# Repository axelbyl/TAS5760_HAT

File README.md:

# TAS5760 based Amplifier HAT for Raspberry Pi

This repository contains the KiCad files for an audio amplifier based on the class D TI TAS5760 amplifier module.

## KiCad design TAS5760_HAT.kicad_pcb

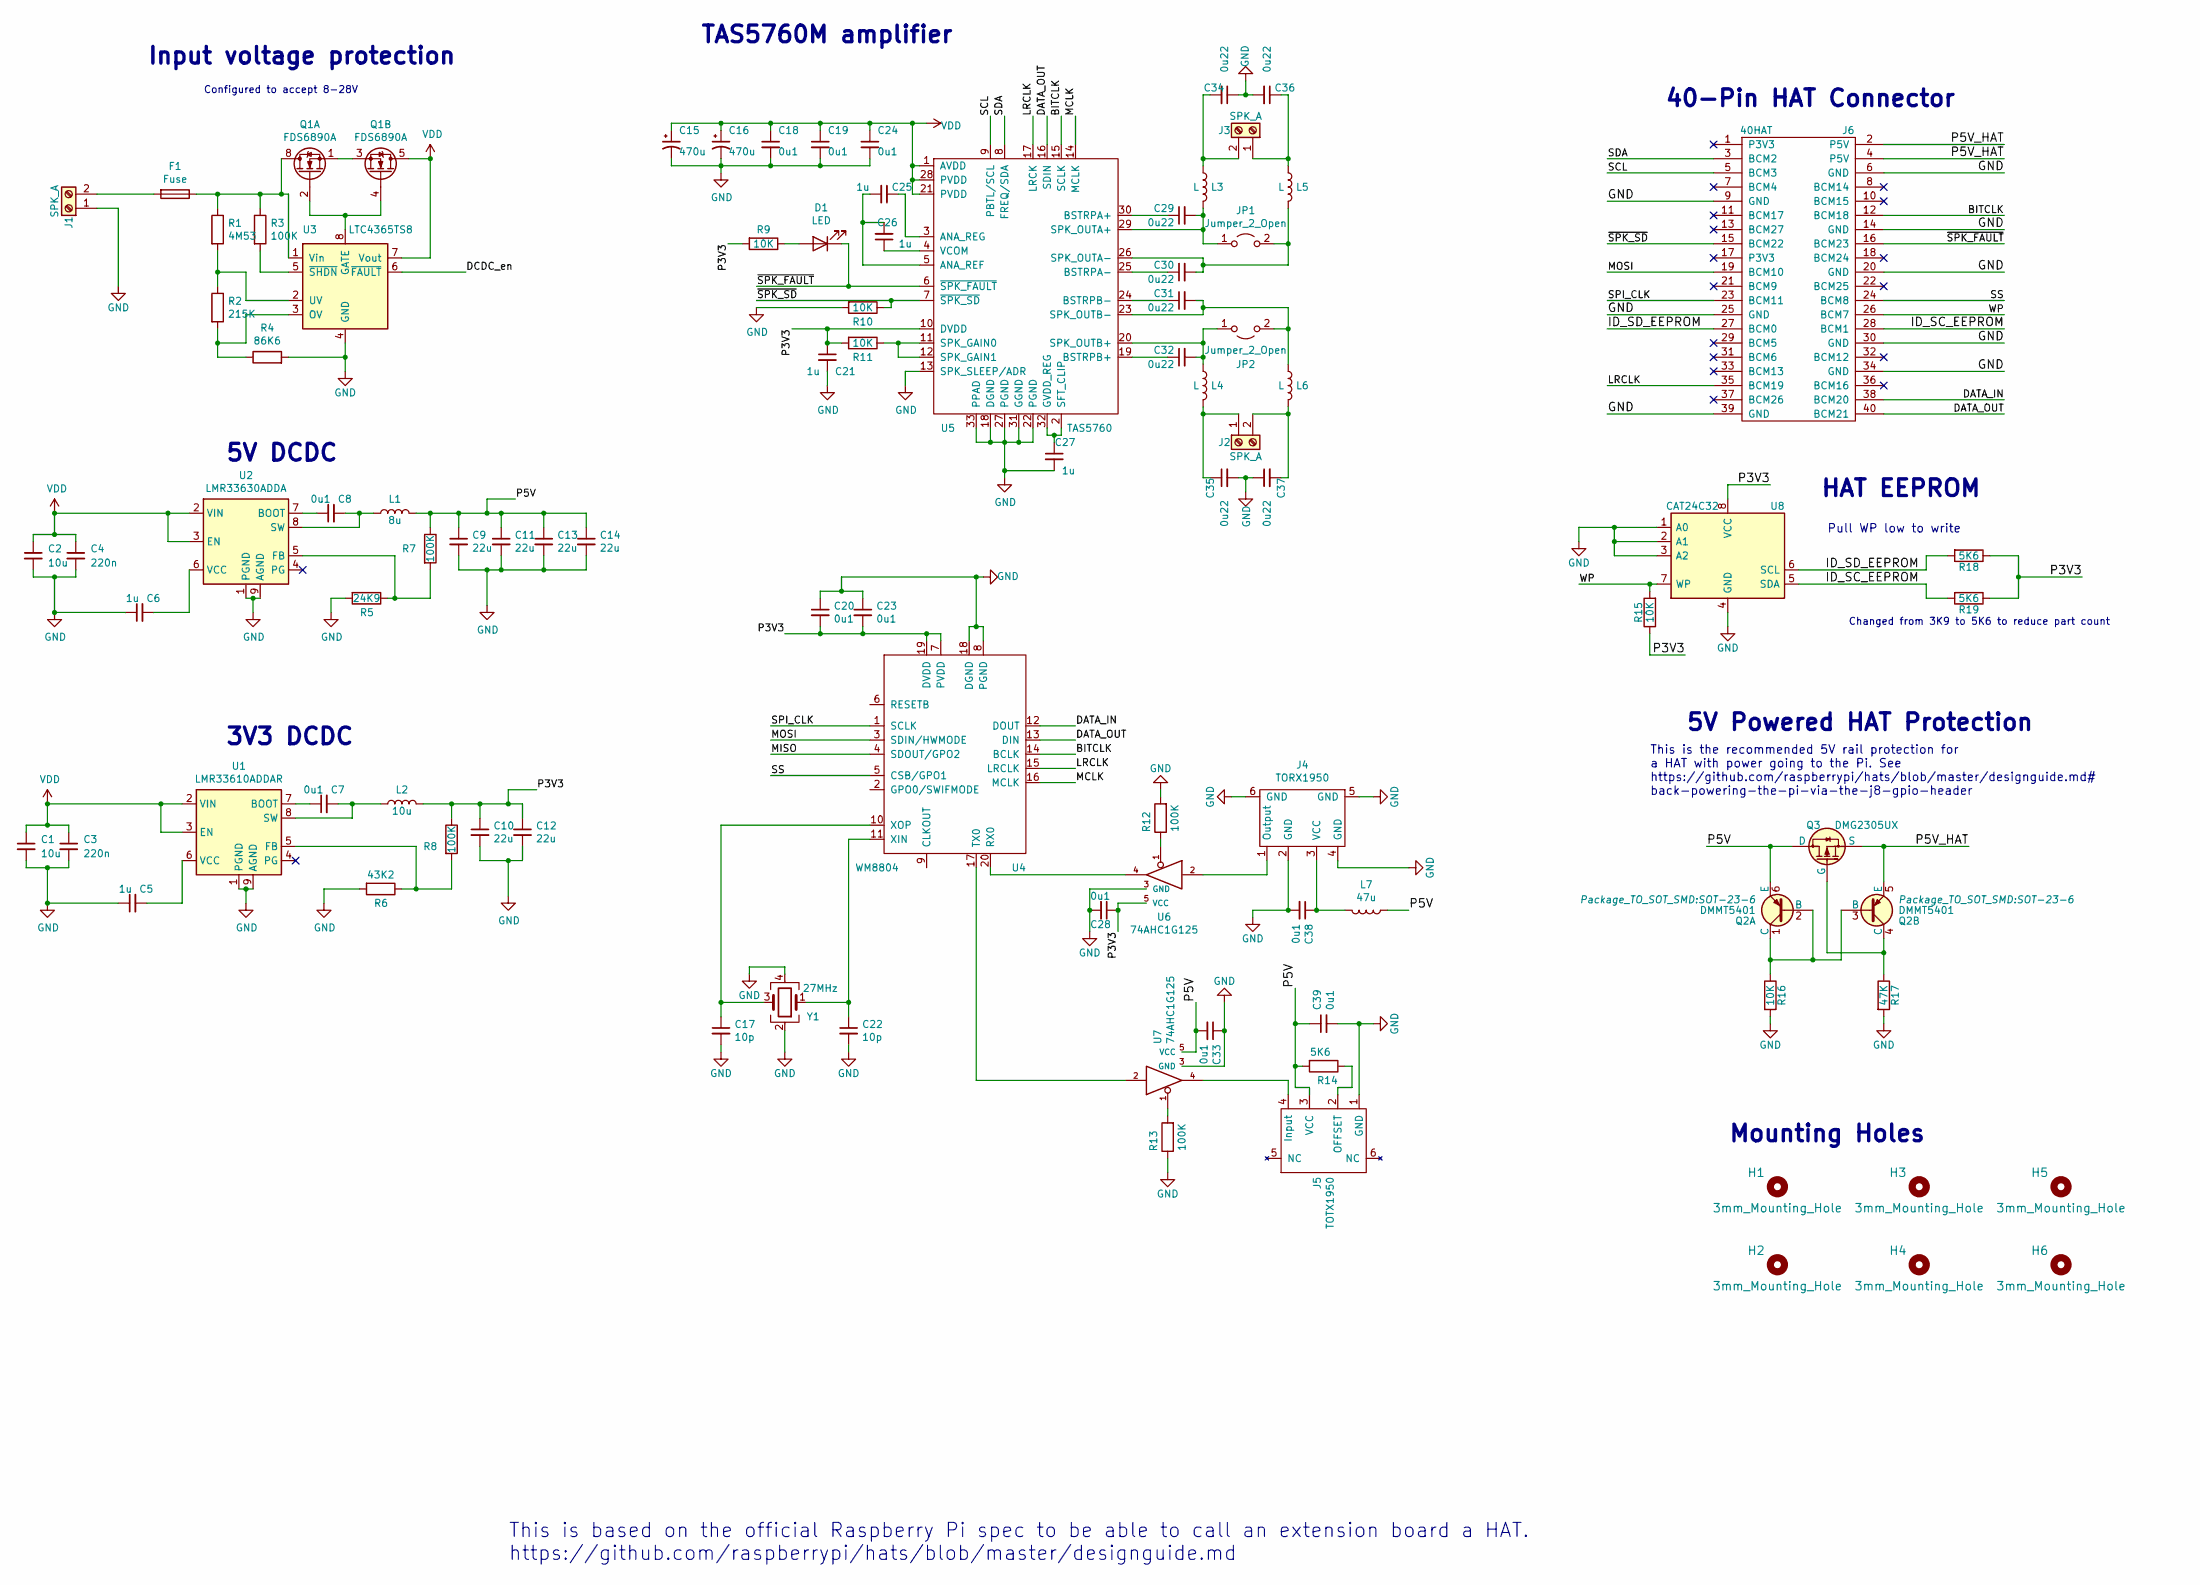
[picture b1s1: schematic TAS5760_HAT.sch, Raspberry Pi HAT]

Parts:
C1, C2: 10u; C_1206_3216Metric
C3, C4: 220n; C_0603_1608Metric
C5, C6, C21, C25, C26, C27: 1u; C_0603_1608Metric
C7, C8, C18, C19, C20, C23, C24, C28, C33, C38, C39: 0u1; C_0603_1608Metric
C9, C10, C11, C12, C13, C14: 22u; C_1206_3216Metric
C15, C16: 470u; CP_Elec_10x10
C17, C22: 10p; C_0603_1608Metric
C29, C30, C31, C32: 0u22; C_0603_1608Metric
C34, C35, C36, C37: 0u22; C_1206_3216Metric
D1: LED; LED_0603_1608Metric
F1: Fuse; FuseHolder_OM_Schurter_OMH_125
H1, H2, H3, H4, H5, H6: 3mm_Mounting_Hole; NPTH_3mm_ID
J1, J2, J3: SPK_A; TerminalBlock_bornier-2_P5.08mm
J4: TORX1950
J5: TOTX1950
J6: 40HAT; PinSocket_2x20_P2.54mm_Vertical
JP1, JP2: Jumper_2_Open; Keystone_Jumper_5102
L1: 8u; L_Bourns_SRN8040TA
L2: 10u; L_Bourns_SRN6045TA
L3, L4, L5, L6: L; L_12x12mm_H8mm
L7: 47u; L_0805_2012Metric
Q1: FDS6890A; SOIC-8_3.9x4.9mm_P1.27mm
Q2: DMMT5401; SOT-23-6
Q3: DMG2305UX; SOT-23
R1: 4M53; R_0603_1608Metric
R2: 215K; R_0603_1608Metric
R3, R7, R8, R12, R13: 100K; R_0603_1608Metric
R4: 86K6; R_0603_1608Metric
R5: 24K9; R_0603_1608Metric
R6: 43K2; R_0603_1608Metric
R9, R10, R11: 10K; R_0603_1608Metric
R14: 5K6; R_0603_1608Metric
R15, R16: 10K; R_0603_1608Metric; MPN RC0402JR-0722RL
R17: 47K; R_0603_1608Metric; MPN RC0402JR-0722RL
R18, R19: 5K6; R_0603_1608Metric; MPN RC0402JR-0722RL
U1: LMR33610ADDAR; Texas_HSOP-8-1EP_3.9x4.9mm_P1.27mm_ThermalVias
U2: LMR33630ADDA; Texas_HSOP-8-1EP_3.9x4.9mm_P1.27mm_ThermalVias
U3: LTC4365TS8; TSOT-23-8
U4: WM8804; SSOP-20_5.3x7.2mm_P0.65mm
U5: TAS5760; HTSSOP-32_backsolder
U6, U7: 74AHC1G125; TSSOP-5
U8: CAT24C32; SOIC-8_3.9x4.9mm_P1.27mm
Y1: 27MHz; Crystal_SMD_SeikoEpson_FA238-4Pin_3.2x2.5mm

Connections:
/BITCLK: J6.12 (BCM18), U4.14 (BCLK), U5.15 (SCLK)
/DATA_IN: J6.38 (BCM20), U4.12 (DOUT)
/DATA_OUT: J6.40 (BCM21), U4.13 (DIN), U5.16 (SDIN)
/DCDC_en: U3.6 (~FAULT)
/ID_SC_EEPROM: J6.28 (BCM1), R19.2, U8.5 (SDA)
/ID_SD_EEPROM: J6.27 (BCM0), R18.2, U8.6 (SCL)
/LRCLK: J6.35 (BCM19), U4.15 (LRCLK), U5.17 (LRCK)
/MCLK: U4.16 (MCLK), U5.14 (MCLK)
/MISO: U4.4 (SDOUT/GPO2)
/MOSI: J6.19 (BCM10), U4.3 (SDIN/HWMODE)
/P3V3: C10.1, C12.1, C20.2, C21.1, C23.2, C28.1, L2.2, R8.1, R9.2, R11.2, R15.1, R18.1, R19.1, U4.7 (PVDD), U4.19 (DVDD), U5.10 (DVDD), U6.5 (VCC), U8.8 (VCC)
/P5V: C9.1, C11.1, C13.1, C14.1, C33.2, C39.1, J5.3 (VCC), L1.2, L7.1, Q2.6 (E), Q3.3 (D), R7.1, R14.2, U7.5 (VCC)
/P5V_HAT: J6.2 (P5V), J6.4 (P5V), Q2.5 (E), Q3.2 (S)
/SCL: J6.5 (BCM3), U5.9 (PBTL/SCL)
/SDA: J6.3 (BCM2), U5.8 (FREQ/SDA)
/SPI_CLK: J6.23 (BCM11), U4.1 (SCLK)
/SS: J6.24 (BCM8), U4.5 (CSB/GPO1)
/WP: J6.26 (BCM7), R15.2, U8.7 (WP)
/~SPK_FAULT: D1.1 (K), J6.16 (BCM23), U5.6 (~SPK_FAULT)
/~SPK_SD: J6.15 (BCM22), R10.1, U5.7 (~SPK_SD)
GND: C1.2, C2.2, C3.2, C4.2, C5.1, C6.1, C9.2, C10.2, C11.2, C12.2, C13.2, C14.2, C15.2, C16.2, C17.2, C18.2, C19.2, C20.1, C21.2, C22.2, C23.1, C24.2, C27.2, C28.2, C33.1, C34.1, C35.2, C36.2, C37.1, C38.2, C39.2, J1.1, J4.2 (GND), J4.4 (GND), J4.5 (GND), J4.6 (GND), J5.1 (GND), J6.6 (GND), J6.9 (GND), J6.14 (GND), J6.20 (GND), J6.25 (GND), J6.30 (GND), J6.34 (GND), J6.39 (GND), R4.2, R5.2, R6.2, R10.2, R12.2, R13.1, R16.2, R17.2, U1.1 (PGND), U1.9 (AGND), U2.1 (PGND), U2.9 (AGND), U3.4 (GND), U4.8 (PGND), U4.18 (DGND), U5.13 (SPK_SLEEP/ADR), U5.18 (DGND), U5.22 (PGND), U5.27 (PGND), U5.31 (GGND), U5.33 (PPAD), U6.3 (GND), U7.3 (GND), U8.1 (A0), U8.2 (A1), U8.3 (A2), U8.4 (GND), Y1.2, Y1.4
unnamed: C5.2, U1.6 (VCC)
unnamed: C6.2, U2.6 (VCC)
unnamed: C7.1, U1.7 (BOOT)
unnamed: C7.2, L2.1, U1.8 (SW)
unnamed: C8.1, U2.7 (BOOT)
unnamed: C8.2, L1.1, U2.8 (SW)
unnamed: C17.1, U4.10 (XOP), Y1.3
unnamed: C22.1, U4.11 (XIN), Y1.1
unnamed: C25.1, U5.3 (ANA_REG)
unnamed: C25.2, C26.2, U5.5 (ANA_REF)
unnamed: C26.1, U5.4 (VCOM)
unnamed: C27.1, U5.2 (SFT_CLIP), U5.32 (GVDD_REG)
unnamed: C29.1, U5.30 (BSTRPA+)
unnamed: C29.2, JP1.1 (A), L3.2, U5.29 (SPK_OUTA+)
unnamed: C30.1, U5.25 (BSTRPA-)
unnamed: C30.2, JP1.2 (B), L5.2, U5.26 (SPK_OUTA-)
unnamed: C31.1, U5.24 (BSTRPB-)
unnamed: C31.2, JP2.2 (B), L6.1, U5.23 (SPK_OUTB-)
unnamed: C32.1, U5.19 (BSTRPB+)
unnamed: C32.2, JP2.1 (A), L4.1, U5.20 (SPK_OUTB+)
unnamed: C34.2, J3.2, L3.1
unnamed: C35.1, J2.1, L4.2
unnamed: C36.1, J3.1, L5.1
unnamed: C37.2, J2.2, L6.2
unnamed: C38.1, J4.3 (VCC), L7.2
unnamed: D1.2 (A), R9.1
unnamed: F1.1, Q1.7 (D1), Q1.8 (D1), R1.1, R3.1, U3.1 (Vin)
unnamed: F1.2, J1.2
unnamed: J4.1 (Output), U6.2
unnamed: J5.2 (OFFSET), R14.1
unnamed: J5.4 (Input), U7.4
unnamed: Q1.1 (S1), Q1.3 (S2)
unnamed: Q1.2 (G1), Q1.4 (G2), U3.8 (GATE)
unnamed: Q2.1 (C), Q2.2 (B), Q2.3 (B), R16.1
unnamed: Q2.4 (C), Q3.1 (G), R17.1
unnamed: R1.2, R2.1, U3.2 (UV)
unnamed: R2.2, R4.1, U3.3 (OV)
unnamed: R3.2, U3.5 (~SHDN)
unnamed: R5.1, R7.2, U2.5 (FB)
unnamed: R6.1, R8.2, U1.5 (FB)
unnamed: R11.1, U5.11 (SPK_GAIN0), U5.12 (SPK_GAIN1)
unnamed: R12.1, U6.1
unnamed: R13.2, U7.1
unnamed: U4.17 (TX0), U7.2
unnamed: U4.20 (RX0), U6.4
VDD: C1.1, C2.1, C3.1, C4.1, C15.1, C16.1, C18.1, C19.1, C24.1, Q1.5 (D2), Q1.6 (D2), U1.2 (VIN), U1.3 (EN), U2.2 (VIN), U2.3 (EN), U3.7 (Vout), U5.1 (AVDD), U5.21 (PVDD), U5.28 (PVDD)

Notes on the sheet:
5V Powered HAT Protection
This is the recommended 5V rail protection for a HAT with power going to the Pi. See https://github.com/raspberrypi/hats/blob/master/designguide.md# back-powering-the-pi-via-the-j8-gpio-header
HAT EEPROM
Mounting Holes
40-Pin HAT Connector
Pull WP low to write
This is based on the official Raspberry Pi spec to be able to call an extension board a HAT. https://github.com/raspberrypi/hats/blob/master/designguide.md
Configured to accept 8-28V
Input voltage protection
5V DCDC
3V3 DCDC
TAS5760M amplifier
Changed from 3K9 to 5K6 to reduce part count

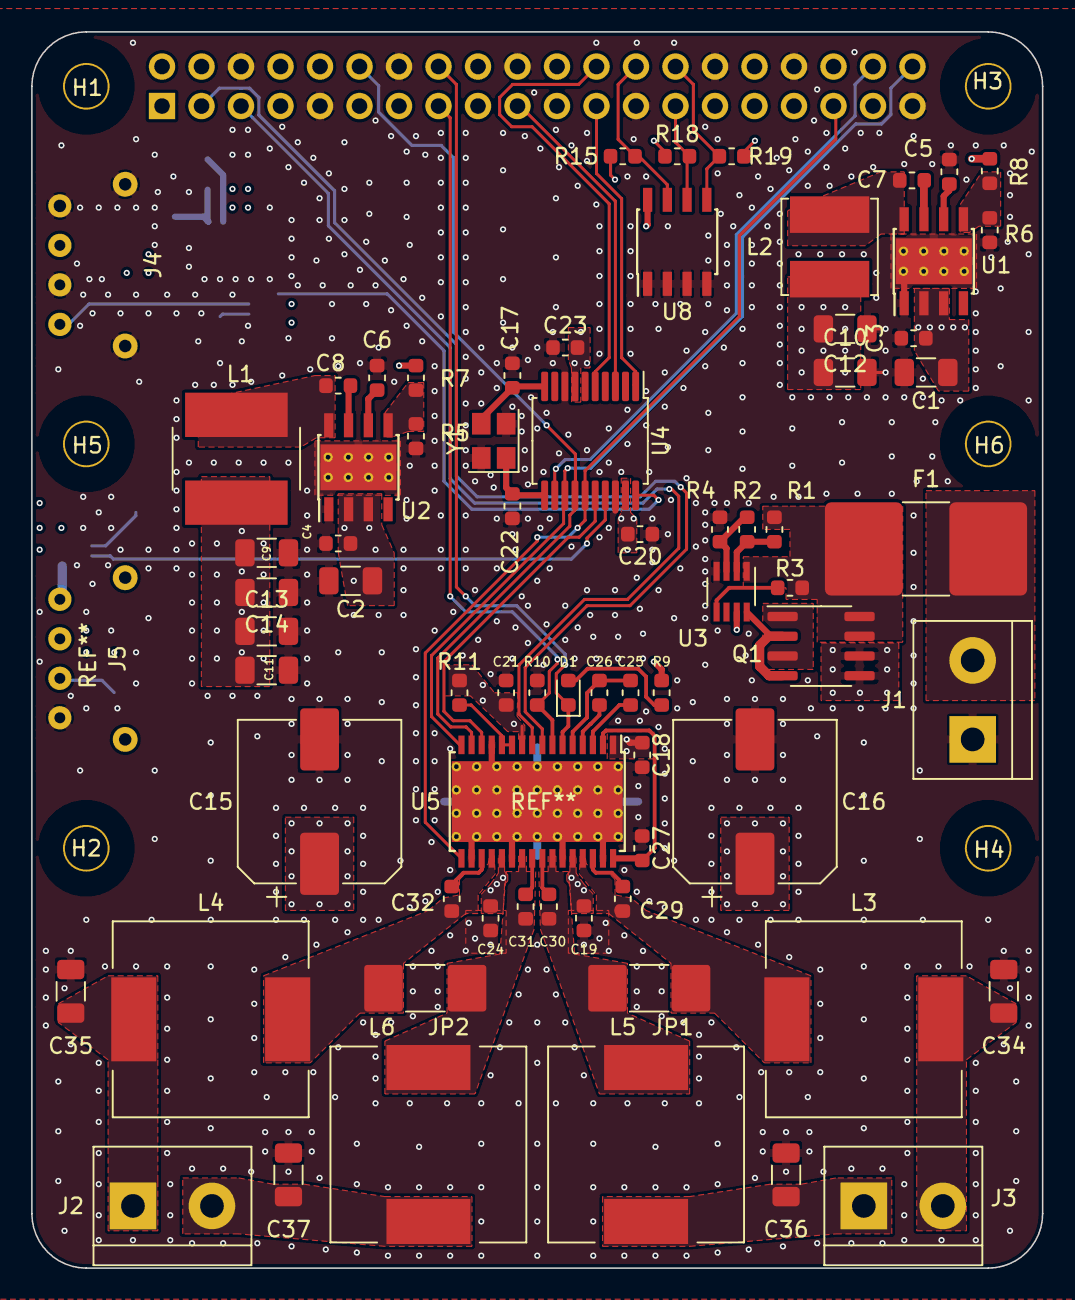
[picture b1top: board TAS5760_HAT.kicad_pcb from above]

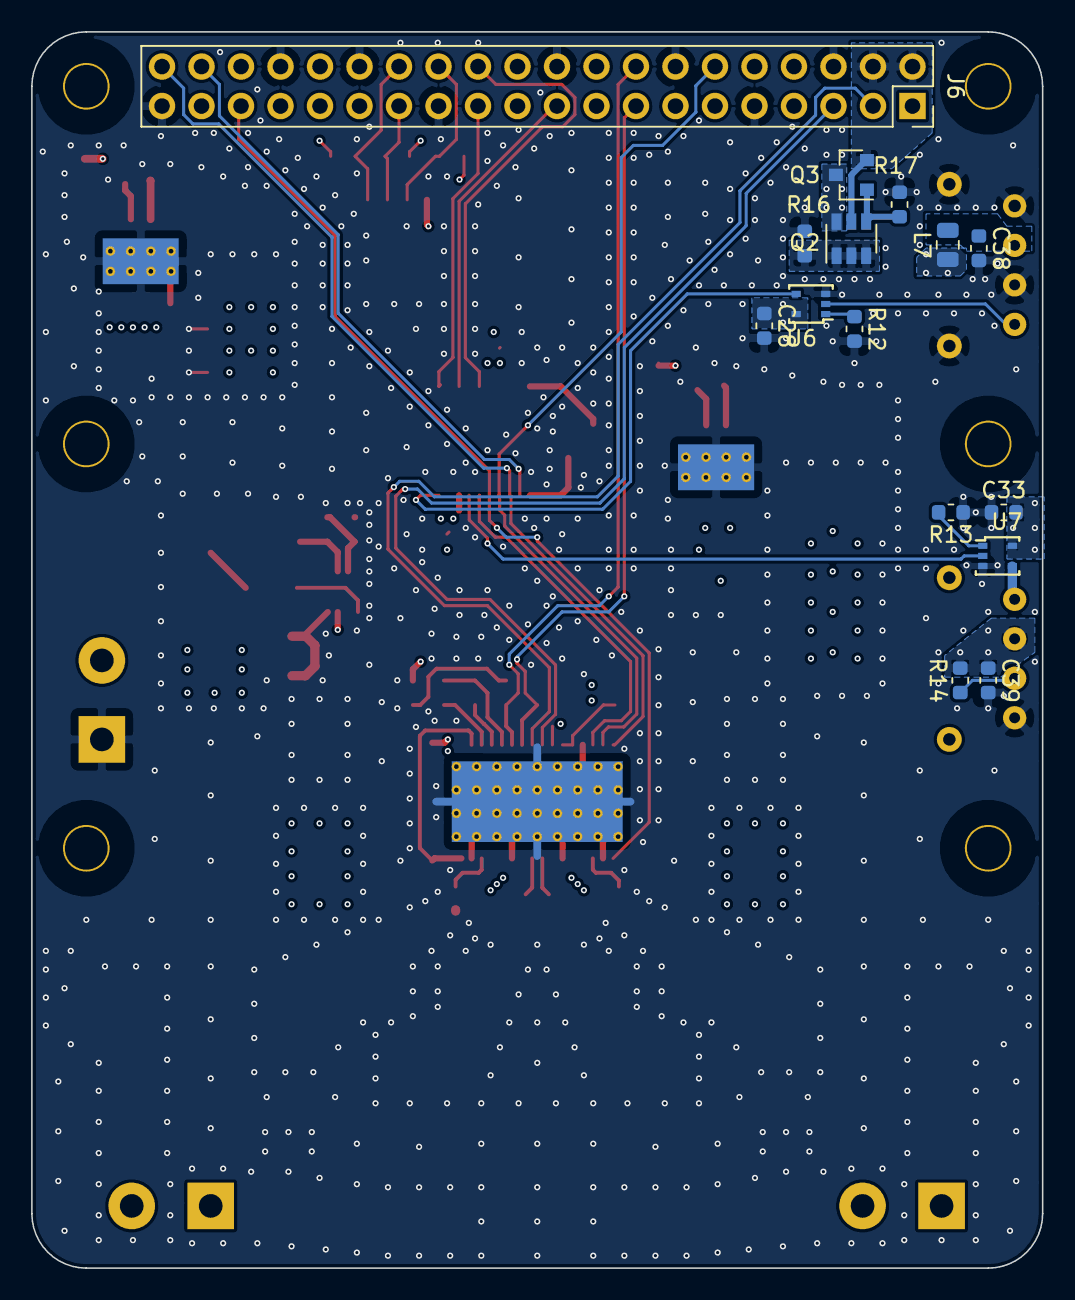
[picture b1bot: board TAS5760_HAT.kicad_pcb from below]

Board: 4 copper layers, 65.0 x 79.5 mm, 93 parts (15 on the bottom side), 65 nets.

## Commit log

2021-01-21 4 flip flops
    Design with four flip flops and pll1708
    Audio output jumper before filter
2021-10-11 Updated clock circuit to WM8804
    Added optional toslink input and output since wm8804 has digital
    input and output. Removed old clock dividing circuit since not needed
    since wm8804 has this for free
